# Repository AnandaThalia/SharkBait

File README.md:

# SharkBait

SharkBait is an Atmega2560 minimum system development project, complete with its RTC circuits and data loggers. And equipped with two connectors for interfacing with sensors

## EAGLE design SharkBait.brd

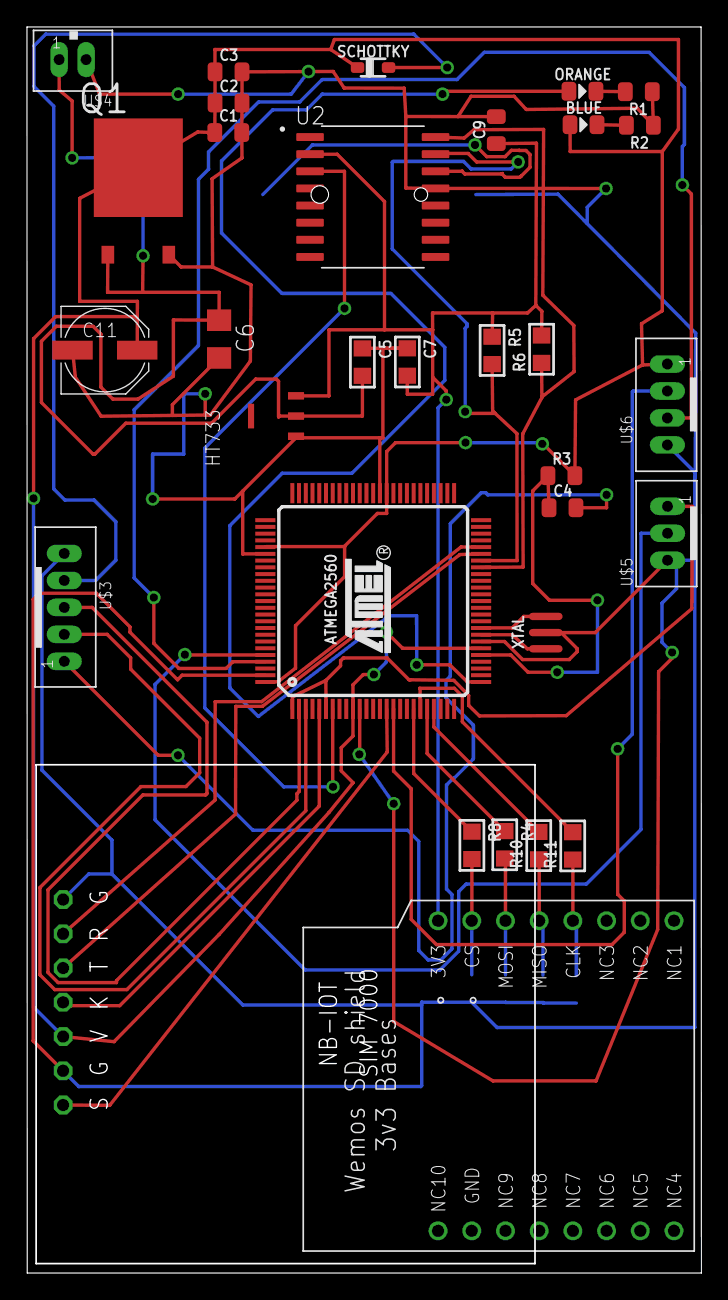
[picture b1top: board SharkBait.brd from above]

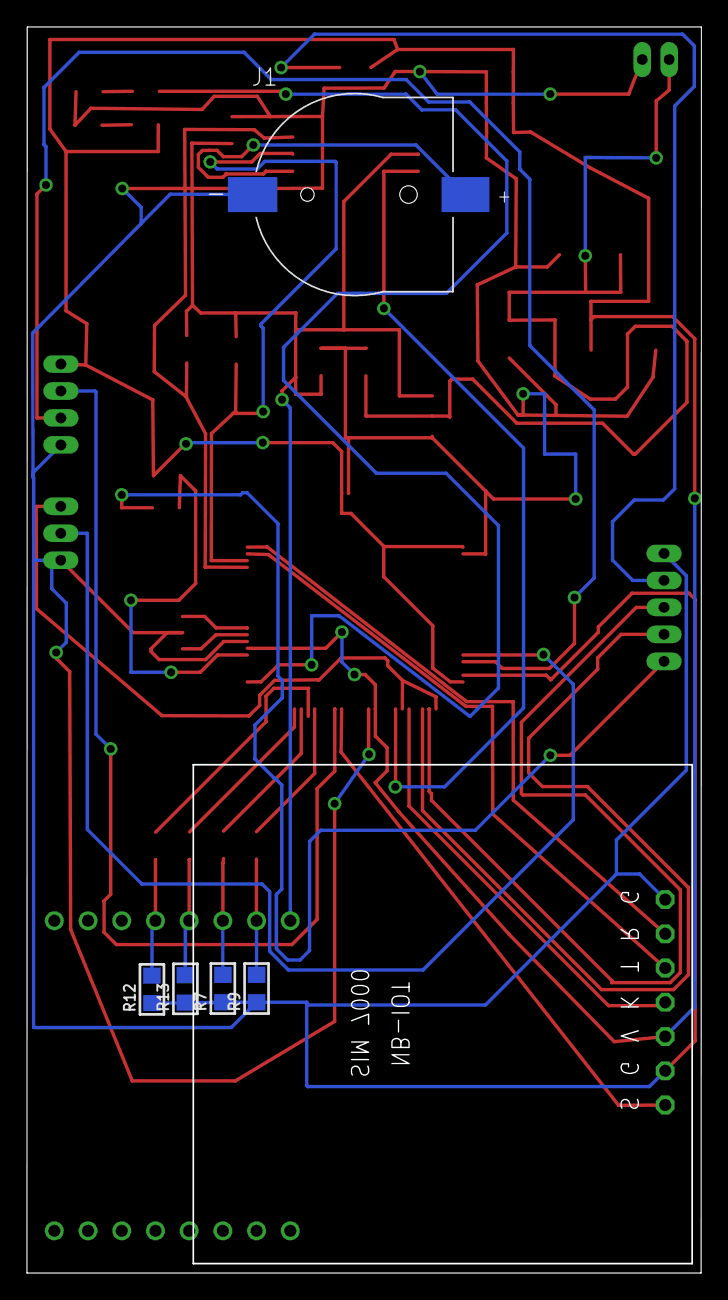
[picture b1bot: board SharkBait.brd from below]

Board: 2 copper layers, 50.0 x 92.4 mm, 37 parts (5 on the bottom side), 32 nets.

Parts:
ATMEGA2560: ATMEGA2560; TQFP100
BLUE: L; SMD-0805-LED
C1: SMD-0805
C2, C3, C4: .1uF; SMD-0805
C5, C7: 100 uF; C0805
C6: 100nF; C1206
C9: 10uF; SMD-0805
C11: 100uF; PANASONIC_D
HT733: HT7333; SOT89
J1: BC501SM-TR; MPD_BC501SM-TR
ORANGE: L; SMD-0805-LED
Q1: L78M05CDT; TO225P972X240-3N
R1, R2, R3: 10k; SMD-0805
R4, R8, R10, R11: 1K8; R0805
R5, R6: R0805
R7, R9, R12, R13: 3K3; R0805
SCHOTTKY: DIODE; SOD-323
U2: DS3231M+; SOIC127P1032X265-16N
U$1: WEMOS_SD_D1_MINI
U$2: SIM7000; SIM_7000
U$3: JST-PH_5-PIN_HEADER; JST_B5B-PH_HEADER
U$4: JST-PH_2-PIN_HEADER; JST_B2B-PH_HEADER
U$5: JST-PH_3-PIN_HEADER; JST_B3B-PH_HEADER
U$6: JST-PH_4-PIN_HEADER; JST_B4B-PH_HEADER
XTAL: 16M; RESONATOR

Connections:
3V3: C7.2, C9.1, HT733.VOUT, R5.1, R6.2, U2.2, U$1.3V3
5V: ATMEGA2560.10, ATMEGA2560.31, ATMEGA2560.61, ATMEGA2560.80, ATMEGA2560.100, BLUE.1, C1.1, C2.1, C3.1, C11.+, Q1.2, R3.2, SCHOTTKY.C, U$2.5V, U$6.P1
A0: ATMEGA2560.97, U$6.P3
A1: ATMEGA2560.96, U$5.P2
D3: ATMEGA2560.7, U2.3
D4: ATMEGA2560.1, ATMEGA2560.6, U$5.P1
D5: ATMEGA2560.5, U$2.KEY
D6: ATMEGA2560.15, U$2.SLEEP
D7: ATMEGA2560.16, U$6.P2
D13: ATMEGA2560.26, ORANGE.1
DTR: C4.2, U$3.P1
GND: ATMEGA2560.11, ATMEGA2560.32, ATMEGA2560.62, ATMEGA2560.81, ATMEGA2560.99, C1.2, C2.2, C3.2, C5.1, C6.2, C7.1, C9.2, C11.-, HT733.GND, J1.-, Q1.3, R1.1, R2.1, R7.1, R9.1, R12.1, R13.1, U2.13, U$2.GND, U$2.GND1, U$3.P5, U$4.P2, U$5.P3, U$6.P4, XTAL.2
MISO: ATMEGA2560.22, R10.1, R10.2, R13.2, U$1.MOSI
MOSI: ATMEGA2560.21, R4.1
unnamed: J1.+, U2.14
unnamed: R4.2, R7.2, U$1.MISO
unnamed: ATMEGA2560.34, XTAL.3
unnamed: ATMEGA2560.33, XTAL.1
unnamed: ORANGE.2, R1.2
unnamed: BLUE.2, R2.2
RST: ATMEGA2560.30, C4.1, R3.1
RX0: ATMEGA2560.2, U$3.P3
RX1: ATMEGA2560.45, U$2.TX
SCK: ATMEGA2560.20, R11.1, R11.2, R12.2, U$1.CLK
SCK1: R8.2, R9.2, U$1.CS
SCL: ATMEGA2560.43, R6.1, U2.16
SDA: ATMEGA2560.44, R5.2, U2.15
SS: ATMEGA2560.19, R8.1
TX0: ATMEGA2560.3, U$3.P2
TX1: ATMEGA2560.46, U$2.RX
VBAT: C5.2, C6.1, HT733.VIN, Q1.1, U$4.P1
VCC: SCHOTTKY.A, U$3.P4

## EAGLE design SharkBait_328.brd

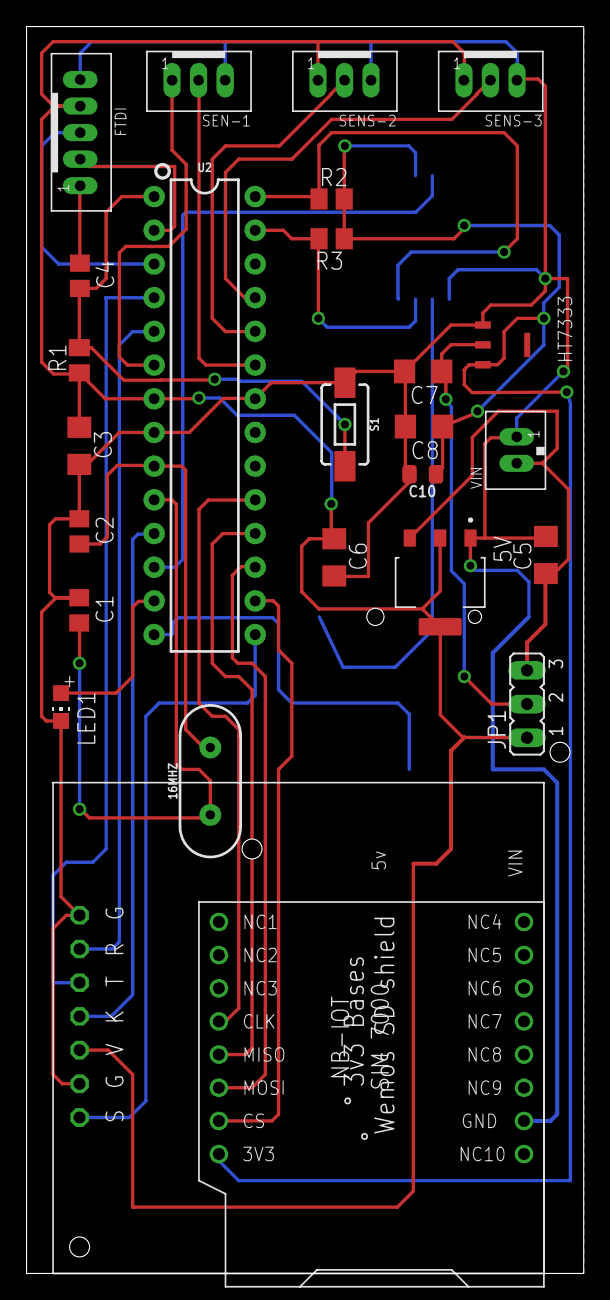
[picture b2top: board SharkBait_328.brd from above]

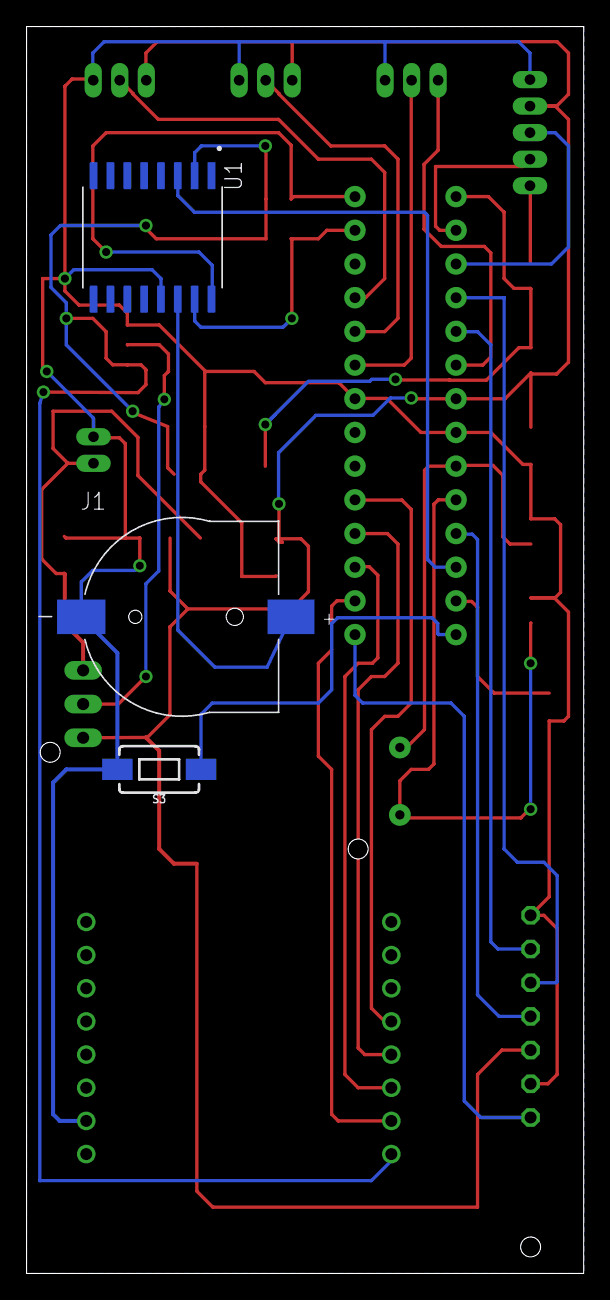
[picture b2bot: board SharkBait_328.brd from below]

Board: 2 copper layers, 42.0 x 94.0 mm, 29 parts (3 on the bottom side), 29 nets.

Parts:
5V: AMS1117; SOT229P700X180-4N
16MHZ: HC49US
C1, C2: 22 pF; C0805
C3: 10 uF; C1206
C4: 100 nF; C0805
C5, C6, C7, C8: 100 uF; C1206
C10: 10uF; SMD-0805
FTDI: JST-PH_5-PIN_HEADER; JST_B5B-PH_HEADER
HT7333: HT7333; SOT89
J1: BC501SM-TR; MPD_BC501SM-TR
JP1: JP2
LED1: CHIP-LED0805
R1, R2, R3: 10 k; M0805
S1, S3: MOMENTARY-SWITCH-SPST-SMD-6.0X3.5MM; TACTILE_SWITCH_SMD_6.0X3.5MM
SEN-1: JST-PH_3-PIN_HEADER; JST_B3B-PH_HEADER
SENS-2, SENS-3: JST-PH_3-PIN_HEADER; JST_B3B-PH_HEADER
U1: DS3231M+; SOIC127P1032X265-16N
U2: 328P; DIP28
U$1: WEMOS_SD_D1_MINI
U$2: SIM7000; SIM_7000
VIN: JST-PH_2-PIN_HEADER; JST_B2B-PH_HEADER

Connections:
3V3: C8.1, C10.1, HT7333.VOUT, R2.2, R3.1, U1.2, U$1.3V3
5V: 5V.2, 5V.4, C3.1, C6.1, FTDI.P4, JP1.1, R1.1, SENS-2.P1, SENS-3.P1, U2.7, U$2.5V
A0: SEN-1.P2, U2.23
A1: SENS-2.P2, U2.24
A2: SENS-3.P2, U2.25
CS: U2.16, U$1.CS
D4-POWSENS: SEN-1.P1, U2.6
D6: U1.3, U2.12
DTR: C4.1, FTDI.P1
GND: 5V.1, C1.1, C2.1, C3.2, C5.2, C6.2, C7.2, C8.2, C10.2, FTDI.P5, HT7333.GND, J1.-, LED1.C, S1.1, S3.2, SEN-1.P3, SENS-2.P3, SENS-3.P3, U1.13, U2.8, U2.22, U$1.GND, U$2.GND, U$2.GND1, VIN.P1
HT-VIN: C7.1, HT7333.VIN, JP1.2
KEY: U2.11, U$2.KEY
MISO: U2.18, U$1.MISO
MOSI: U2.17, U$1.MOSI
unnamed: 16MHZ.2, C2.2, U2.9
unnamed: 16MHZ.1, C1.2, U2.10
unnamed: J1.+, U1.14
unnamed: LED1.A, U2.13
unnamed: S3.1, U2.14
unnamed: C4.2, R1.2, S1.2, U2.1
RX: FTDI.P2, U2.2
RX-SIM: U2.4, U$2.TX
SCK: U2.19, U$1.CLK
SCL: R2.1, U1.16, U2.28
SDA: R3.2, U1.15, U2.27
SLEEP: U2.15, U$2.SLEEP
TX: FTDI.P3, U2.3
TX-SIM: U2.5, U$2.RX
VIN: 5V.3, C5.1, JP1.3, VIN.P2

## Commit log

2019-11-10 Sistem minimum Atmega2560
2019-11-10 menambahkan pin uploader
2019-11-13 Revisi final
2019-11-13 routing
2019-11-13 brd version 1
2019-11-16 revisi 3, termasuk pembetulan pin yang terbalik, dan regulator 5v yang terbalik
2019-11-16 file dengan level shifter
2019-11-16 layout dengan level shifter
2019-11-19 rejuvination
2019-11-19 pembuatan folder
2019-12-21 Create code
2020-01-06 board utk 328
2020-01-06 remove folder
2020-01-06 brd and sch files
2020-01-06 repair rtc
2020-01-07 routing v1
2020-01-07 terlalu rapet

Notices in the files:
parts and their libraries:
rc-master-smd: Copyright (C) 2007, Bob Starr
SparkFun-IC-Microcontroller: Licensing: Creative Commons ShareAlike 4.0 International - https://creativecommons.org/licenses/by-sa/4.0
